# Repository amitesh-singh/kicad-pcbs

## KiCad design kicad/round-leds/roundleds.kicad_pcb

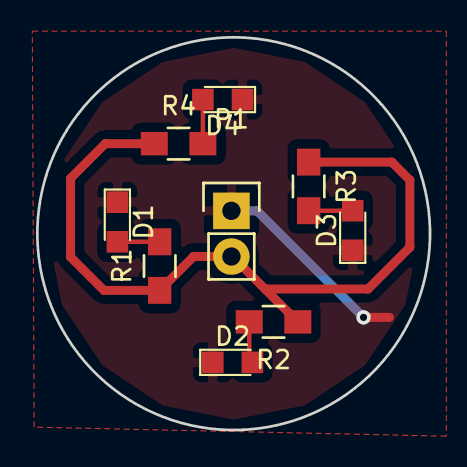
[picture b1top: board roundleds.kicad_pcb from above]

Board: 2 copper layers, 21.8 x 21.8 mm, 9 parts (0 on the bottom side), 6 nets.

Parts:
D1, D2, D3, D4: LED; LED_0805
P1: CONN_01X02; Pin_Header_Straight_1x02
R1, R2, R3, R4: R; R_0805_HandSoldering

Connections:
GND: D1.1, D2.1, D3.1, D4.1, P1.1
unnamed: D1.2, R1.2
unnamed: D2.2, R2.2
unnamed: D3.2, R3.2
unnamed: D4.2, R4.2
VCC: P1.2, R1.1, R2.1, R3.1, R4.1

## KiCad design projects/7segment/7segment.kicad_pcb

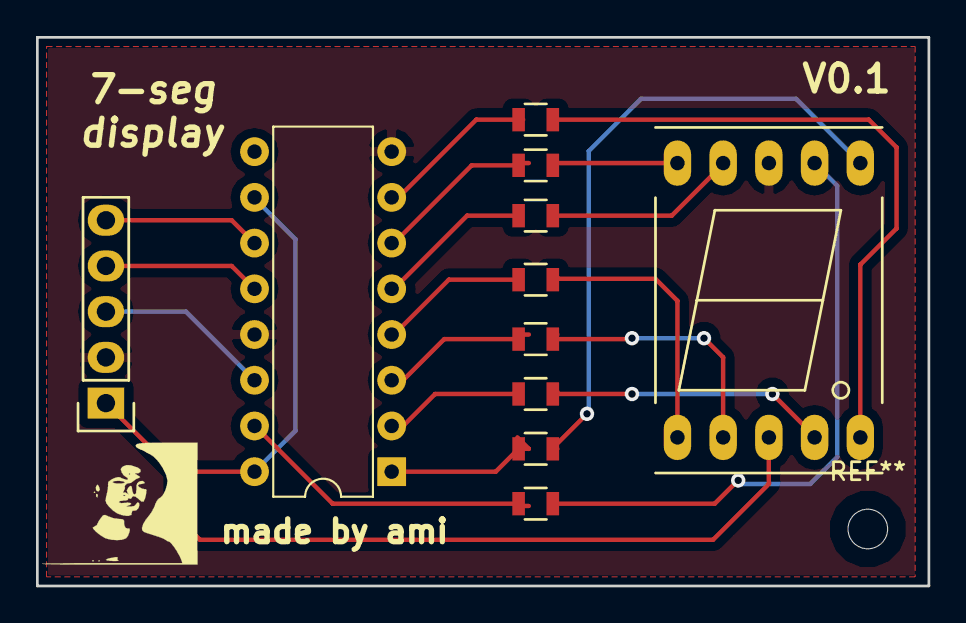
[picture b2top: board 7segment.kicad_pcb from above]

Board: 2 copper layers, 49.5 x 30.5 mm, 11 parts (0 on the bottom side), 21 nets.

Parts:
P1: CONN_01X05; Socket_Strip_Straight_1x05
R1, R2, R3, R4, R5, R6, R7, R8: 220; R_0805
S1: 7SEGM; 7SegmentLED_LTS6760_LTS6780
U1: 74HC595; DIP-16_W7.62mm

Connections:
/CLOCK: P1.4, U1.12
/DATA: P1.5, U1.11
/LATCH: P1.3, U1.14
/seg0: R8.1, U1.15
/seg1: R7.1, U1.1
/seg2: R6.1, U1.2
/seg3: R5.1, U1.3
/seg4: R4.1, U1.4
/seg5: R3.1, U1.5
/seg6: R2.1, U1.6
/seg7: R1.1, U1.7
GND: P1.2, S1.8, U1.8, U1.13
unnamed: R1.2, S1.5
unnamed: R2.2, S1.10
unnamed: R3.2, S1.9
unnamed: R4.2, S1.1
unnamed: R5.2, S1.2
unnamed: R6.2, S1.4
unnamed: R7.2, S1.6
unnamed: R8.2, S1.7
VCC: P1.1, S1.3, U1.10, U1.16

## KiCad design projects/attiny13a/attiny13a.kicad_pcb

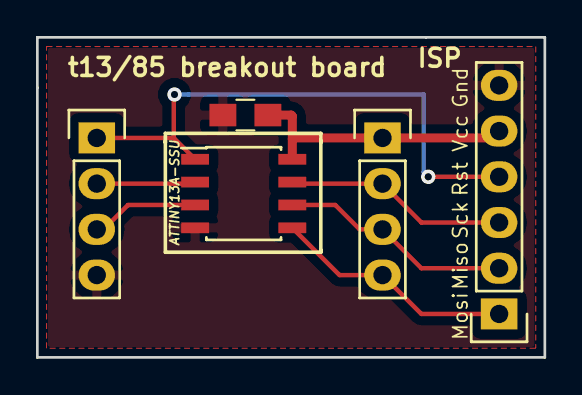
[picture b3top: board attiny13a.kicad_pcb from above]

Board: 2 copper layers, 28.2 x 17.8 mm, 5 parts (0 on the bottom side), 8 nets.

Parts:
C1: C; C_0805_HandSoldering
P1, P2: CONN_01X04; Socket_Strip_Straight_1x04
P3: CONN_01X06; Socket_Strip_Straight_1x06
U1: ATTINY13A-SSU; SOIC-8_3.9x4.9mm_Pitch1.27mm

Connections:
/pb0: P1.4, P3.1, U1.5
/pb1: P1.3, P3.2, U1.6
/pb2: P1.2, P3.3, U1.7
/pb3: P2.2, U1.2
/pb4: P2.3, U1.3
/rst: P2.1, P3.4, U1.1
GND: C1.2, P2.4, P3.6, U1.4
VCC: C1.1, P1.1, P3.5, U1.8

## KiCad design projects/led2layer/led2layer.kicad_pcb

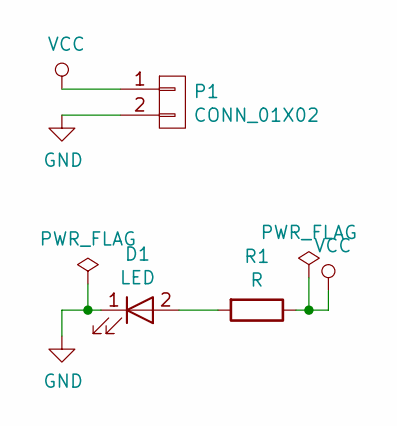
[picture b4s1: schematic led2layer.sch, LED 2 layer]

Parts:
D1: LED; LED_D3.0mm
P1: CONN_01X02; Harwin_LTek-Male_02x2.00mm_Straight_StrainRelief
R1: R; Resistor_SMDuniversal_0805to1206_HandSoldering

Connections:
GND: D1.1 (K), P1.2
unnamed: D1.2 (A), R1.2
VCC: P1.1, R1.1

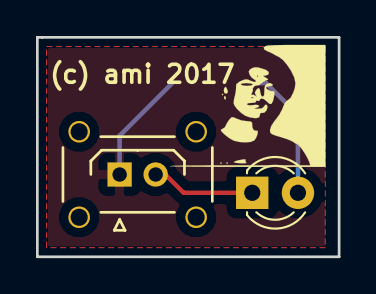
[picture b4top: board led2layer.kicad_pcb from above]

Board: 2 copper layers, 16.8 x 12.2 mm, 3 parts (1 on the bottom side), 3 nets.

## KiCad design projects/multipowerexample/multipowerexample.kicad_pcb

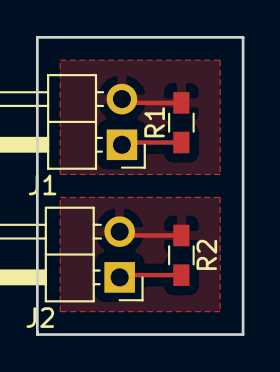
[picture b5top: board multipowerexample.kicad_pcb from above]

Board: 2 copper layers, 11.4 x 16.5 mm, 4 parts (0 on the bottom side), 4 nets.

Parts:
J1, J2: Conn_01x02; Pin_Header_Angled_1x02_Pitch2.54mm
R1, R2: R; R_0603_HandSoldering

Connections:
GND: J2.2, R2.1
GND2: J1.2, R1.2
VCC: J2.1, R2.2
VCC2: J1.1, R1.1

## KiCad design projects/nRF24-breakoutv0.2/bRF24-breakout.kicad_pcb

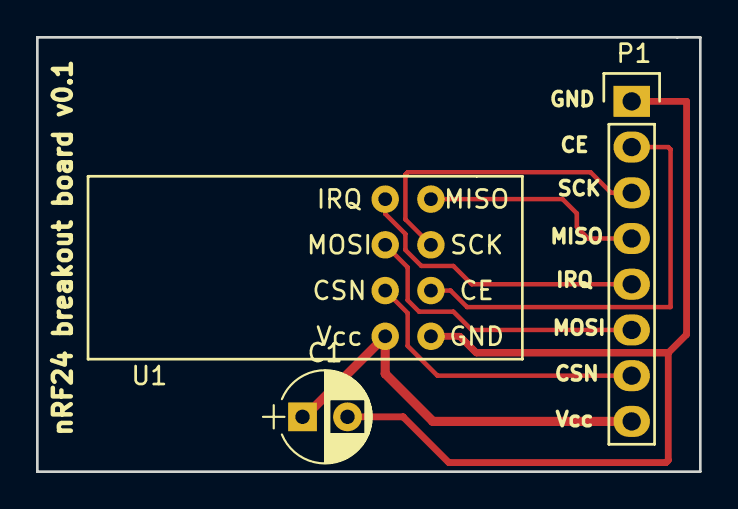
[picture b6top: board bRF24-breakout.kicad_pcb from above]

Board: 2 copper layers, 36.8 x 24.1 mm, 3 parts (0 on the bottom side), 8 nets.

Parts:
C1: 10uF; CP_Radial_D5.0mm_P2.50mm
P1: CONN_01X08; Socket_Strip_Straight_1x08
U1: nRF24

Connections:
unnamed: C1.1, P1.8, U1.7
unnamed: C1.2, P1.1, U1.0
unnamed: P1.2, U1.1
unnamed: P1.3, U1.2
unnamed: P1.4, U1.3
unnamed: P1.5, U1.4
unnamed: P1.6, U1.5
unnamed: P1.7, U1.6
